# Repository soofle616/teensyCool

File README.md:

# teensyCool
Code, mechanical, and electrical design files for teensyCool automatic adjustable coolant nozzle for Tormach milling machines

This repository contains files to recreate the teensyCool by SmellyDog automatic adjustable coolant nozzle for Tormach milling machines. This project replicates the function and largely recreates the aesthetic of the SmartCool adjustable coolant nozzle available from Tormach. Additional information and installation instructions will periodically be added to this README as time permits. 

Programming the teensy can be accomplished using Teensyduino within the Arduino IDE: https://www.pjrc.com/teensy/td_download.html

Installation on a Tormach mill requires installation of 99-teensy.rules to /etc/udev/rules in PathPilot.

Thanks to Jon Watte for his serial parsing routine used in his USBIO emulator found here: https://github.com/jwatte/teensy_tormach_usbio

All files and designs are Copyright 2021 Ian Vivero, released under GNU GPLV3.0

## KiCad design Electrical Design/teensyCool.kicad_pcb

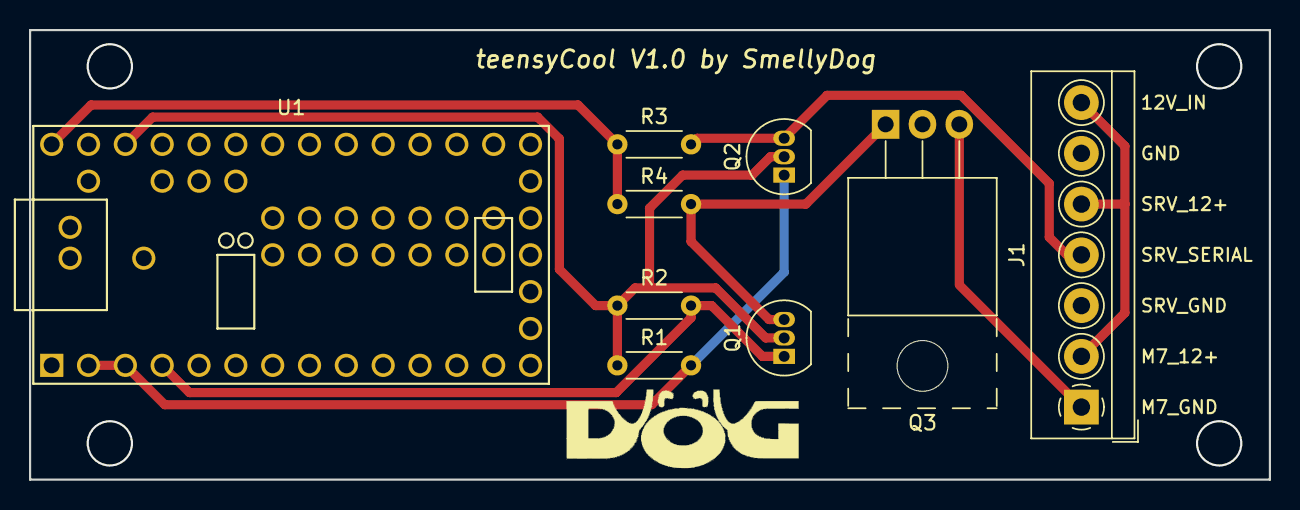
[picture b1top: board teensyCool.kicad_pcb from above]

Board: 2 copper layers, 85.5 x 31.0 mm, 9 parts (0 on the bottom side), 9 nets.

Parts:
J1: Screw_Terminal_01x07; TerminalBlock_4Ucon_1x07_P3.50mm_Horizontal
Q1, Q2: 2N7000; TO-92_Inline
Q3: RFP30N06LE; TO-220-3_Horizontal_TabUp
R1, R2, R3, R4: 10k; R_Axial_DIN0204_L3.6mm_D1.6mm_P5.08mm_Horizontal
U1: Teensy3.2; Teensy30_31_32_All_Pins

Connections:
/3.3V: Q1.2, Q2.2, R1.1, R2.1, U1.31
/5V: R3.1, R4.1, U1.33
/12V: J1.2, J1.5, J1.7
GND: J1.3, J1.6, Q3.2, U1.1
unnamed: J1.1, Q3.3
unnamed: J1.4, Q2.3, R3.2
unnamed: Q1.1, R2.2, U1.4
unnamed: Q1.3, Q3.1, R4.2
unnamed: Q2.1, R1.2, U1.2, U1.3

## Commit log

2021-02-25 Add files via upload
    Source code, KiCad design files and label graphics uploaded
2021-06-22 Add dynamixel library
    Add arduino library files for dynamixel library to control the servo. Source/Author of library unknown
2021-06-26 Add .rules file
